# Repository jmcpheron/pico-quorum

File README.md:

<p align="center">
  <picture>
    <source media="(prefers-color-scheme: dark)" srcset="docs/brand/lockup-dark.svg">
    <source media="(prefers-color-scheme: light)" srcset="docs/brand/lockup-light.svg">
    
  </picture>
</p>

<p align="center">
  <strong>Several people, several keys, one Safe.</strong><br>
  Hardware approvals for <a href="https://safe.global">Safe</a> multisig wallets.
</p>

<p align="center">

  <br>

  <br>

</p>

Picoquorum is a small console that is **one owner of a Safe**. Each signer holds a plug-in key with a
secure element inside. The console shows what a transaction does on its own screen, works out the
Safe transaction hash itself, and asks the key to sign only after you have seen every page and held
the green **Sign** button. **Reject** is red and easy.

The same console also runs [in your browser](https://picoquorum.app/console/), with
your own passkey as its key. That version is one short folder you can read, check against this
README, and sign from on your own computer.

### A pico quorum

A *pico quorum* is a small group that agrees before anything moves: a family's savings, a club's
treasury, a two-person company, a project's release keys. Two of three. Three of five. Too small for
a custody desk, too important for one laptop. Picoquorum gives each person in that group the same
small box and their own key, and makes every approval a deliberate thing you do with your hands.

> **Experimental.** Early design. Use a testnet first, and only small amounts on mainnet. The Safe's
> threshold is the real control: always keep owners on the Safe that are not this console.

## Four ideas

### 1. A key that can't leak

The key is a secure element on a small board you plug in. Its P-256 private key is generated inside
the chip, never leaves it, and never exists as a seed phrase. There is nothing to write down,
photograph or phish. The chip has no command that reads a private key out, it is locked after
provisioning, and the console asks it to sign only a hash the console worked out itself.

Each key owns the Safe through Safe's audited passkey signer
([`firmware/webauthn.py`](firmware/webauthn.py)), with the same owner address on every chain. The
contracts it relies on were checked onchain on Base and Ethereum.

**The USB-C key, in production now.** [key-c P2](hardware/key-pcb/key-c-usbc/README.md) is the key
as a part you can hold: an ATECC608C behind a USB-C receptacle on a 16 × 36 mm board, with an ESD
array between the connector and the chip.
- The receptacle is plain wires, not USB: D+ carries SDA, D− carries SCL, and VBUS is key power
  that the console switches on only when the key is fully in.
- 5.1 kΩ on each CC pin tells the console a key is present.
- Five boards are being assembled at JLCPCB; the first bench bring-up is next.

| parts side | back |
|---|---|
|  |  |

Until it arrives, the dev console's key is an Infineon OPTIGA Trust M or an ATECC608 breakout. The
other key designs (card edge, pogo pads) are in [`hardware/key-pcb/`](hardware/key-pcb/README.md).
How a chip is locked: [docs/LOCKING.md](docs/LOCKING.md) and [docs/TRUSTM.md](docs/TRUSTM.md).
What a sealed key can't protect you from: [docs/SECURITY.md](docs/SECURITY.md).

### 2. A simple console that checks on its own

The console is a Raspberry Pi Pico 2 W with a 240 × 240 screen and a few buttons, running a small
amount of MicroPython you can read. It doesn't take anyone's word for a transaction: not your
laptop's, not your browser's, not Safe{Wallet}'s, and not the transaction service's.

- **Its own hash.** It rebuilds the Safe's EIP-712 transaction hash from the fields it shows, for
  the chain and Safe it was set up for, and its key signs that hash and nothing else. A service
  that lies about the hash, the Safe or the chain gets a refusal, not a signature.
- **Its own words.** It decodes each call into plain language. Anything that changes who controls
  the Safe, or can't be undone, is a red page, red all over.
- **Its own screen.** You page through every screen before Sign is allowed, then hold it for two
  seconds. The verify code (the hash's last eight characters and its blockie) is there to check
  with whoever proposed it.
- **Its own path.** It talks to the transaction service over its own Wi-Fi and TLS, checking
  certificates against the roots it carries. Nothing on your computer is in the loop.

| | | | |
|---|---|---|---|
|  |  |  |  |
| **Plain language.** What it does, who it pays, who has signed. | **Red pages.** Owners, thresholds, anything that can't be undone. | **A verify code.** To check with the proposer. | **Hold to sign.** Two seconds on a guarded button. |

That independence is the point. A second check is only worth something if it fails differently from
the first: different hardware, different code, a different network path, a different person looking
at it. More screens: [docs/quorum-ui](docs/quorum-ui/README.md).

**The console on its own board.** [console-rp](hardware/console-rp/README.md) is
the console as one board: an RP2350A with no radio, a 1.14″ 240 × 135 screen, D0 D1 D2 under it,
and an ATECC608C on the board. Its USB-C reaches only a CH343P serial chip, never the RP2350's own
USB or its REPL.
- Five came assembled from JLCPCB on 2026-11-04. Four run the console's own image and one is
  broken ([the boards](hardware/console-rp/README.md#the-boards-and-the-firmware)).
- The owner makes the key on the board, and the console pins itself to that chip
  ([setting one up](hardware/console-rp/SETUP.md)).
- With no Wi-Fi, a relay on the computer fetches the Safe's queue and posts the console's
  signatures: `tools/relay/relay.py`, or the app's Device page. The console still rebuilds every
  hash itself ([the relay](docs/USB-LINK.md#the-relay-console-rp)).

### 3. One owner in a multisig

Picoquorum is never the whole wallet. It is one owner among several, and it is built to sit next to
the others: a hardware wallet, a passkey, Safe{Wallet} in a browser, another Picoquorum in another
house. The project's own Safe is planned around one rule ([docs/GOVERNANCE.md](docs/GOVERNANCE.md)),
and we suggest it for yours: **no technology, and no person, holds a threshold's worth of keys.**

- **Standard Safe.** Any Safe from 1.3.0 on, on Base and Ethereum. Propose anywhere; the console
  reads the same queue Safe{Wallet} does.
- **The app** ([launch it](https://picoquorum.app/app/)) opens any Safe, proposes,
  checks every confirmation in your browser, and executes with your wallet. It holds no key.
- **Several Safes, several chains.** One console watches up to 4 Safes on Base Sepolia, Base and
  Ethereum, with one queue across them ([networks](docs/guide/NETWORKS.md)).
- **A pico quorum per Safe.** A family Safe at 2 of 3, a team Safe at 3 of 5, each owner with a
  console and a key of their own.

### 4. A short stack you can check yourself

[The console page](https://picoquorum.app/console/) runs the console's firmware,
file for file, on MicroPython for WebAssembly, with your passkey (Touch ID, Windows Hello, a phone,
a security key) as its key. It is one folder, it loads nothing from the rest of the site, and it can
reach only Safe's transaction service: its Content-Security-Policy says so, and the browser enforces
it.

| in the folder | |
|---|---|
| `firmware/` | the console image a Pico runs, as plain files: about 11,000 lines of MicroPython |
| `shims/` | Python in place of the Pico's hardware: about 630 lines |
| `console.js`, `worker.js`, `web/`, `core/` | the page: about 1,100 lines of JavaScript |
| `vendor/micropython/` | MicroPython 1.26 for WebAssembly, pinned by its hash: the one part built elsewhere |

That is short enough to read, and you can check it without trusting the site that sent it:
- **Save a copy.** `SHA256SUMS` lists every file: fetch them, then `sha256sum -c SHA256SUMS`. There
  is no build step; these are the files that run.
- **Hold it up to this README.** `firmware/`, hashed with `sha256sum` in a one-line loop, gives the
  console's release fingerprint in [the build table](#the-build-youre-looking-at): the same one a
  Pico running that release shows on its Device screen.
- **Rebuild it.** `cd emu && npm ci && node build.mjs` writes the same bytes. CI checks that on every
  push, and a check from outside compares what Pages serves with the source every six hours.
- **Sign from your copy.** Run `python3 -m http.server` in the folder and open `localhost:8000`. A
  passkey belongs to the site that made it, so one made on your copy can be asked to sign by your
  copy and never by a later version of the site. Its owner address works on a Safe like any other.

The commands: [docs/guide/BROWSER.md](docs/guide/BROWSER.md). The screen is still drawn by your
computer, and the passkey's prompt never shows the transaction, so the hardware console is the
stronger owner: keep passkey owners below the threshold.

## Try it

- **[The site](https://picoquorum.app/)**, with the app.
- **[The console in your browser](https://picoquorum.app/console/)**: the same
  firmware in MicroPython on WebAssembly, with your own passkey as its key. Save it, check it and
  run your own copy ([how](docs/guide/BROWSER.md); the design: [EMU-WEB.md](docs/EMU-WEB.md)).
- **[Learn](https://picoquorum.app/learn/)**: short explainer videos on why a multisig and what the
  console adds to one. The videos are on their way; [their scripts](docs/videos/README.md) are here
  to read.
- **[The owner's guide](docs/guide/README.md)**: from a board to a console that signs for your
  Safes.
- **Build a dev console**: a Pico 2 W, a Waveshare Pico-LCD-1.3 and an ATECC608 breakout, about
  $35 with no soldering ([build guide](hardware/DEV-CONSOLE.md), [parts](hardware/bom/README.md)).
- **On a laptop**, no hardware: `tools/quorum e2e` runs a whole approval with the emulator against a
  Safe 1.4.1 on an Anvil fork of Base ([details](tools/mock-tx-service/README.md)).
- **The hash, checked**: `python3 test-vectors/run.py` runs every vector in
  [`test-vectors/`](test-vectors/), including real mainnet Safe transactions, on CPython; CI runs
  them on MicroPython 1.26 too.

## The build you're looking at

Every firmware image has a **release fingerprint**: one SHA-256 over its source files
([docs/releases](docs/releases/README.md)). A console shows its blockie and first 8 hex digits on the
Device screen; the console page shows the same picture for the same files, and its `firmware/`
folder hashes to it with `sha256sum` ([how](docs/guide/BROWSER.md#2-hold-it-up-to-the-readme)); the
app's Releases page lists each release's. The badges above and this table name the source in this commit, so you can hold a
console up to the README:

<!-- build:begin (node tools/releases/badge.mjs writes this table) -->

| | image | release fingerprint |
|---|---|---|
|  | **console** | `c79cac3145ff41a832656c4eeebad22e4f8dc3719f27e9f5acd9be9e41572275` |
|  | **ceremony** | `381d4e8916ea331b7b8a8ef650b28c5a45d35c116fe40969c8f5c66cea223ec2` |
|  | **brand** | `f7b49688d24a2ce8dbc4f5af474a708f4b043af84049aa9b56221c76f1b9ceb3` |
|  | **dual** | `99292ecee02cdcabfd1714b7c16ab250634345925e9c6cd2764c10589be48d55` |
|  | **console-rp** | `f24d22db5f3916c11f6bbcc5a934885ea6593c7a132d318e042c1f4617094505` |
|  | **prepare-rp** | `4e98165819acdbb148753a1e73cb04bb83bec7861b4263e9246b60531162999f` |

<!-- build:end -->

How a release is trusted ([docs/RELEASES.md](docs/RELEASES.md)):
- **Signed tags.** A release is an SSH-signed tag, `fw-<version>`, checked against
  [`.github/allowed_signers`](.github/allowed_signers) before anything is built.
- **Reproducible pages.** CI rebuilds the app and the console page from source and fails if they
  differ from what is committed. The site check then compares what GitHub Pages serves, byte for byte,
  with the commit it deployed.
- **Approved by a Safe.** The project Safe will approve each release on chain, signed on Picoquorum
  consoles, and the app then shows **Approved by the project Safe**. The code is ready; the Safe
  comes at launch ([docs/GOVERNANCE.md](docs/GOVERNANCE.md)).

## Where it stands

Picoquorum is built in public. **[docs/STATUS.md](docs/STATUS.md)** is the one page for what exists
today: the name (picoquorum.eth) and the domains, every Safe and key with its address, the contracts
the console relies on, and what's next.

**Now:** [console-rp](hardware/console-rp/README.md), the one-board console with no radio. Its
firmware runs on four boards and is in review (pull request #113).

The [test ladder](docs/LADDER.md) tracks each chain:
- ✅ a simulated Safe and a local fork, on the real Pico
- ✅ Base Sepolia, end to end over HTTPS on the real Pico
- Base with a few dollars: the Safe is checked and a chip's confirmation has executed there; the
  console's own approval is next
- then Ethereum mainnet, whose contracts have been checked onchain

The design and the open questions are in the [kickoff](docs/KICKOFF.md), and the project Safe's plan
in [GOVERNANCE.md](docs/GOVERNANCE.md). Dated notes and photos, mistakes included, are in
[`buildlog/`](buildlog/).

## Layout

| path | what |
|---|---|
| `firmware/` | the console in MicroPython: `quorum.py` and `quorum_ui.py` (the console), `safe_tx.py` (the Safe hash), `decode.py`, `txservice.py`, `webauthn.py`, the chip drivers `trustm.py` and `atecc.py` |
| `hardware/` | `console-rp/` ([the one-board console](hardware/console-rp/README.md)), `key-pcb/` (the keys, [key-c](hardware/key-pcb/key-c-usbc/README.md) among them), `wiring/` ([Build 1](hardware/wiring/BUILD1.md), [perfboard](hardware/wiring/SOLDERING.md), [breadboard](hardware/wiring/BREADBOARD.md), [on an ESP32](hardware/wiring/ESP32.md)), `bom/` |
| `docs/` | everything to read ([index](docs/README.md)), and the site GitHub Pages serves: the front page, `app/`, `console/`, `brand/` |
| `web/` | the app's source; `npm run build` writes `docs/app/` |
| `emu/` | the console in a browser: MicroPython in WebAssembly and a virtual secure element. `build.mjs` writes the console page (`docs/console/`); `tools/emu` adds an editor and the case in 3D, for development |
| `test-vectors/` | Safe transactions with known-correct hashes, and the suites CI runs |
| `tools/` | `quorum` (Safes on a fork and on chain), `fw` (build and push images), `emu`, `usb`, `release`, `releases/`, `brand/`, `keypcb`, `wiring`, `wiring-esp32` |
| `contracts/` | Picoquorum's own contracts, when there are any; today each key owns a Safe through Safe's passkey signer |
| `buildlog/` | dated notes and photos |

The name, the mark and the colours: [docs/BRAND.md](docs/BRAND.md). `tools/brand/lockup.py` draws the
logo at the top of this page.

## Credit

Picoquorum exists because of [picowallet](https://github.com/austintgriffith/picowallet) by
**Austin Griffith**. picowallet proved that a Raspberry Pi Pico can drive a secure element from
MicroPython, rebuild an EIP-712 digest on the device, show it on its own screen, and sign with a
key that never leaves the chip, all on mainnet. Picoquorum began as a fork of it and is still
built on it:
- the ATECC608 and Trust M drivers, the display driver, keccak and P-256, blockies and the WiFi join;
- the emulator that runs the console in your browser.

Each of those files says so on its first line, under Austin's MIT license. Fixes to the drivers go
back upstream ([docs/UPSTREAM-TRACKING.md](docs/UPSTREAM-TRACKING.md)). Everything else this project
uses is credited in [NOTICE](NOTICE).

Picoquorum runs on Raspberry Pi Pico 2 W. It is not affiliated with Raspberry Pi or Safe.

## License

| | license |
|---|---|
| Code and firmware: `firmware/`, `emu/`, `web/`, `tools/`, `test-vectors/`, the built site | [MIT](LICENSE) |
| Hardware: `hardware/` (the key boards, wiring, parts lists) | [CERN-OHL-W-2.0](LICENSE-HARDWARE) |
| Docs, the build log, photos and screenshots | [CC BY-SA 4.0](LICENSE-DOCS) |
| The name Picoquorum and its mark | not licensed: [TRADEMARK.md](TRADEMARK.md) |

Hardware made from these sources must show where the source is ([hardware/README.md](hardware/README.md#license)).
Third-party parts and their licenses are in [NOTICE](NOTICE).

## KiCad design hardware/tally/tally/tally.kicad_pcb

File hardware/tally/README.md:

# Tally: a second take on Mono's idea, with no inductor

*Design, 2026-11-13. Written by a script, [gen_tally.py](gen_tally.py), with KiCad 7.0.11: KiCad
reads the schematic back (netlist) and runs its DRC on the routed board, and both come out clean.
Ten agents then reviewed it; what they found and what was changed is in [REVIEW.md](REVIEW.md).
The repo's own checks (`tools/keypcb check` and `jlc`) want KiCad 10 and were **not run**: see
[What is checked, and how](#what-is-checked-and-how). Not ordered, nothing built, no panel folded
against it, and no firmware profile for it yet. Tally is a working name.*

*The board file's front copper, drawn by a throwaway plotting script that is not in the repository
(KiCad 7 has no 3D render; `tools/keypcb render tally` will make proper ones on KiCad 10). Blue is
signal, red 3.3 V, orange 1.1 V, purple 5 V, grey ground. Pale lines are on the back.
[The back](renders/tally-back.png), seen through the board, is in the same folder.*

Tally is an independent design of the same console as [Mono](../mono/README.md): a 40 × 89.5 mm
bar with no radio, the key soldered on, a small screen for clear signing and three buttons. It
starts from Mono's outline and pins and makes its own choices where Mono's parts are hard to buy or
its first relative, console-rp, misbehaved.

```
   computer (the relay) ── USB-C ── CH343P ── UART1 ── RP2350A ── I2C0 ── ATECC608C (the key that signs)
   no key, no say in                                  │
   what gets signed                                   └─ SPI1 ── 1.14" panel;  D0 D1 D2
   firmware goes in over SWD only: J3 on the front, pads on the back, 100 Ω in each line
```

The computer can't reach the RP2350's REPL, reset it or hold BOOTSEL: the CH343P's modem pins go
nowhere, and the RP2350's own USB pins go nowhere either. The generator checks both
([The link](#the-link)).

## What is different from Mono, and why

| | Mono | Tally | why |
|---|---|---|---|
| the core's 1.1 V | the RP2350's switching regulator: Abracon inductor, 33 Ω, three capacitors | a fixed 1.1 V LDO, **TLV74311PDBVR**, from 3.3 V; one capacitor at the chip's regulator pins | the inductor is the hardest part to buy (JLCPCB 756, LCSC 0, one maker, polarity matters). console-rp's board 1 read 1.4 V on DVDD where 1.1 V is expected, and nobody knows why. An LDO has nothing to lay out wrong. It costs about 0.14 W more from USB at 45 mA of core current |
| the crystal | Abracon ABM8-272-T3, the one Raspberry Pi names | YXC **X322512MSB4SI** (C9002) on Raspberry Pi's 15 pF and 1 kΩ | JLCPCB has 1 of the Abracon, LCSC 0. The YXC is a Basic part with 494,234 in stock. Not Raspberry Pi's tested part: see [Open](#open) |
| the chip's own USB, BOOT | on pads, through 27 Ω and 1 kΩ | **not connected** | console-rp's own USB never enumerated; SWD is how its board 1 was loaded. Three parts and three pads fewer, and one less way in. It has a cost: see [Open](#open) |
| the debug way in | pads for a pogo jig | the same pads at Mono's places, and **J3**, Raspberry Pi's 3-pin JST-SH debug socket | a Debug Probe's cable plugs in. No jig is needed for the first boards |
| the second key's site | KEY 2: a footprint, a switched supply, a header | none | not needed for a first product |
| the USB-C | left of centre | centred | the bridge and the ESD diodes sit in line above it |
| on VBUS | 5.7 µF | 11 µF, as console-rp | WCH asks for 10 µF beside a CH343P fed from VBUS, whose limit is 6.0 V. See [Open](#open) |
| the link's idle level | none until the firmware drives it | 4.7 kΩ to 3.3 V on the chip's TX | the bridge sees a clean idle while the chip is in reset or blank |
| the backlight's driver | an NPN and a base resistor | an N-FET, AO3400A | one part fewer |
| parts | 87 on the drawing, 67 fitted | 70 on the drawing, **53 fitted**, of 25 kinds | |

Kept: the outline, the four M2 holes, the glass and the three buttons where Mono has them; the
RP2350A with Raspberry Pi's copper round it (`rpi_minimal.json`, MIT,
[lib/RPI-MINIMAL-LICENSE.txt](lib/RPI-MINIMAL-LICENSE.txt)); the CH343P link; the ATECC608C in
SOIC-8; the ZIF and the panel; the LDL1117S33R; the backlight fed from 5 V; and **every GPIO**
([PINS.md](PINS.md)), so one board profile can serve console-rp, Mono and Tally.

**Mono's case does not fit as it is.** The board's outline, holes, glass and buttons are Mono's.
The USB-C's opening moves to the middle, the LED is 66.5 mm from the top where Mono's is 71, and
J3 opens toward the left wall. `cad/consoles/mono.py` was not run on Tally and stops on it today
(it has no size for J3's package).

**An ESP32 instead?** No. Every ESP32 that JLCPCB can solder has a radio on the chip except the
ESP32-P4, which needs Standard assembly, costs $5.41, and had 111 in stock. The RP2350A has no radio
on the chip, costs $1.23, and the firmware already runs on it.

## The core's supply

The RP2350 datasheet (section 6.3.7, figure 24) allows it: "If the digital core supply (DVDD) is
powered from an external 1.1 V supply, the on-chip regulator can be disabled and the application
circuit simplified. Power must still be provided on the regulator's analogue supply (VREG_AVDD)
and input supply (VREG_VIN) ... But the inductor can be omitted and only a single input capacitor
is required. Connect VREG_FB directly to ground."

So on Tally:
- VREG_VIN (pin 49) and VREG_AVDD (pin 46) are on 3.3 V with C20, 4.7 µF.
- VREG_FB (pin 50) and VREG_PGND (pin 47) are on ground. VREG_LX (pin 48) is open.
- U4 feeds the three DVDD pins: 4.7 µF at its output, 100 nF at pins 6 and 39, 4.7 µF at pin 23.
- TP10 on the back is DVDD, to put a meter on.

**What the firmware must know**, which it need not on Mono:
1. **Never let the regulator go to its low-power mode.** The datasheet: "Don't put the regulator
   into low-power mode if DVDD is being powered from an external supply." That mode is the reset
   default for the P1.x sleep states (`VREG_LP_ENTRY.MODE` resets to 1). `firmware/` uses no sleep
   today. Before any is used on this board, write `VREG_LP_ENTRY` with HIZ 1 and MODE 0, and find
   out what MicroPython's `lightsleep` does on an RP2350.
2. **`VREG.HIZ` is optional, and not for a shared image.** Left alone, the chip's regulator stays
   on with nothing to drive: "a safe mode of operation, though the regulator will consume
   approximately 400 µA until it's shut down". An image only for Tally can write 1 to `VREG.HIZ`
   on every boot (it does not survive a reset). On Mono or console-rp the same write takes the
   core's supply away: "If the on-chip regulator is supplying DVDD, entering high-impedance mode
   causes a reset event". So an image shared by the three must not write it.

The TLV74311P is ±1.4 % over temperature by its datasheet, so 1.085 to 1.115 V, inside the chip's
1.05 to 1.16 V. It gives 300 mA. Its heat is (3.3 − 1.1) V × the core's current: about 0.1 W at
45 mA. How it holds up under the core's load steps was not measured or simulated.

## The link

The same as Mono's. The USB-C's D+ and D− go through the USBLC6-2SC6 to the CH343P and stop. The
CH343P's TXD and RXD go to GPIO21 and GPIO20 (UART1) and to two pads on the back, to watch the
link. R13 pulls the chip's TX to 3.3 V, so the bridge sees an idle line before the firmware runs.
`gen_tally.py` stops if:
- any pin of the CH343P is on another net than its name allows: TXD on LINK_RX, RXD on LINK_TX,
  VIO on 3.3 V, and DTR, RTS, ACT, DCD, DSR, CTS and RI on nothing at all;
- the RP2350's USB_DP or USB_DM is connected at all;
- the USB-C and the RP2350 share any net but ground;
- any of 23 nets reaches a part that is not on its list: D+, D−, both CC lines, the bridge's V3,
  the link's two lines, SWCLK and SWDIO on each side of their resistors, RUN, the key's bus, the
  three buttons and the flash's six lines.

## The front, top to bottom

- **The panel**, a 1.14-inch 240 × 135 ST7789 (ER-TFT1.14-2) on tape, where Mono has it. Its ribbon
  folds under into J2. Only J2 and two capacitors are under the glass. Four silkscreen corners
  show where the glass goes.
- **D0, D1, D2**, 10 mm apart, 24 mm from the top, as Mono.
- **The backlight's switch** on the left: Q2 (GPIO13, 4.7 kΩ to ground) pulls Q1's gate; Q1 feeds
  the LED from 5 V through 150 Ω, about 13 mA. High is on.
- **The key**, U6, under D1, with its pull-ups and capacitor.
- **The RP2350A**, turned a quarter turn, and **the flash** beside it.
- **U4**, the 1.1 V regulator, under the chip.
- **The red LED** (GPIO25), 66.5 mm from the top.
- **J3**, the debug socket, on the left edge, with 100 Ω in SWCLK and SWDIO.
- **The bridge, the ESD diodes and the USB-C** in line at the bottom; the 3.3 V regulator beside them.

Nothing is fitted on the back. It has the pads and the text.

## The pads on the back

| pad | net | |
|---|---|---|
| TP1, TP2, TP3 | SWCLK, GND, SWDIO | at Mono's places, 2.54 mm apart; on J3's side of the 100 Ω |
| TP4 | RUN | low resets the chip |
| TP5, TP9 | 3V3, GND | to measure |
| TP10 | 1V1 | the core's supply |
| TP11 | VBUS | |
| TP12, TP13 | TX, RX | the link, to watch with a logic probe |

Mono's BOOT, D+ and D− pads have no twin here. No pad has a via at its centre, so a pogo pin lands
on copper.

## Parts at JLCPCB

Read from JLCPCB's and LCSC's listings on 2026-11-13. Stock and prices move daily.

| | part | LCSC | tier | JLCPCB stock | each |
|---|---|---|---|---|---|
| U1 | RP2350A | C42411118 | Extended | 5,813 | $1.29 |
| U7 | W25Q128JVSIQ, 16 MB | C97521 | Basic | 70,193 | $2.26 |
| U6 | ATECC608C-SSHDA-T | C28975195 | Extended | 3,664 | $1.75 |
| U5 | CH343P | C2846043 | Extended | 18,478 | $1.00 |
| U3 | LDL1117S33R | C435835 | Extended | 53,806 | $0.49 |
| U4 | TLV74311PDBVR | C485147 | Extended | 10,900 | $0.07 |
| U2 | USBLC6-2SC6 (ST) | C7519 | Extended | 43,645 | $0.16 |
| J1 | TYPE-C-31-M-12 | C165948 | Extended | 539,075 | $0.19 |
| J2 | 0.5K-HX-8PWB | C2919492 | Extended | 13,441 | $0.10 |
| J3 | SM03B-SRSS-TB | C160403 | Extended | 26,795 | $0.19 |
| Y1 | X322512MSB4SI, 12 MHz | C9002 | Basic | 494,234 | $0.10 |
| Q1, Q2 | AO3401A, AO3400A | C15127, C20917 | Basic | over 1,000,000 each | $0.08 |
| SW1 to SW3 | TS-1187A-B-A-B | C318884 | Basic | 826,275 | $0.02 |
| the rest | 24 capacitors, 12 resistors, 1 LED, all 0402 but four | | Basic | | $0.17 together |

- **About $8.00 of parts a board**, at JLCPCB's price for one.
- **Nine Extended kinds.** On Economic assembly that is 9 × $3.07, with $8.18 setup, $1.53 stencil
  and $0.45: about $38 an order before boards, parts and joints.
- **Two fees could go.** J3 can be left off the BOM (the pads on the back do the same job with a
  jig). JLCPCB lists an SRV05-4 (C7420376) as a Preferred part with no fee, in the USBLC6's package;
  its maker is not ST and its pinout was not checked here, so Tally keeps the ST part.
- **With the flash inside the chip.** `BUILD = "RP2354A"` in the generator fits an RP2354A
  (C41378174, 1,418 in stock, $1.24 at ten) and leaves U7 and its capacitor off: about $2.30 less a board.
  It has 2 MB, so it needs a MicroPython build told so; the stock Pico 2 image assumes 4 MB. The
  default stays the RP2350A with the 16 MB flash, which is what console-rp's board 1 ran.
- The panel is not JLCPCB's: 100 ER-TFT1.14-2 were bought at $3.71.
- **Placement angles.** JLCPCB lays its own footprint for each part on the CPL's point. Eight of
  them have pin 1 in another corner than KiCad's: U2, U4, U5, U6 and U7 need a quarter turn, and U3,
  Q1 and Q2 a half. `cpl.csv` carries those turns. The schematic has them as the field
  `JLCPCB Rotation Offset`, which `tools/keypcb fab` reads too. J1's point is where JLCPCB's
  footprint has its origin, 1.4 mm from KiCad's. All of it comes from JLCPCB's own footprints,
  laid pad for pad on KiCad's, four times over; the published rotation tables agree but for U4
  ([REVIEW.md](REVIEW.md#the-placement-file)). None of it is proven on a board. In JLCPCB's
  placement preview, hold each IC's dot against the silkscreen's mark before paying: **U5 and U1
  first**, where a wrong quarter turn fits every pad; then U6, U7, U2 and D1; then U4.

## Routing

Two layers, 0.15 mm least track and gap, 0.6 mm vias with 0.3 mm holes. Every track is drawn by
the script, by coordinates: nothing was autorouted.
- **Round the chip** the copper is Raspberry Pi's, turned with it: the 3.3 V and 1.1 V rings under
  the chip, each supply pin's track to its capacitor, the crystal's corner. Their switching
  regulator's corner is left out.
- **The back is ground**, with these tracks on it: the 1.1 V tracks under the chip (Raspberry Pi's);
  D0, 18 mm from the chip to the left button; the key's 3.3 V, 8 mm; the screen's DC, 5 mm under the
  glass; 5 V across the bridge; D− for 4 mm under the USB-C; and stubs to five pads. Three of them
  exist because GPIO2, 3 and 6 leave the chip in the opposite order to D0, D1, D2, and Tally keeps
  Mono's pins rather than untangle them.
- **90 ground vias** join the two pours on a 4 mm grid, and one more sits beside each capacitor the
  grid left far from one.
- **5 V runs up the left edge** to the backlight's switch, about 55 mm of 0.25 mm track at 13 mA. It
  passes under R11 between its pads.
- The screen's six lines run 25 mm side by side. SCK has 0.5 mm to its neighbours.

## What is checked, and how

Run here, with KiCad 7.0.11 on Linux, on 2026-11-13:
- `python3 gen_tally.py`: writes everything, then checks it. `python3 gen_tally.py check` checks
  the files as they are. Two runs give the same bytes.
- **The table against itself:** each GPIO can do the job it is given (SPI1, I2C0, UART1); the
  screen's and key's pins are `firmware/board.py`'s Pico defaults; the link's rules above.
- **KiCad's netlist of the schematic against the table:** every net has exactly the pins the table
  lists, every part its value, footprint and LCSC number.
- **The board against the netlist:** every pad on its net, every schematic pin on a pad, every part
  at its place and side.
- **KiCad's DRC on the routed board**, with the project's rules: 0 violations, 0 unconnected.
- **fab/, the project file and PINS.md:** each written again into a temporary folder and compared
  (the Gerbers with their date lines left out).
- **Six broken copies** (TXD and RXD swapped, two screen pins swapped, PINS.md edited, every DRC
  severity set to ignore, the zip replaced, a pad cut from a footprint): the check stops on each.
- **A review** by ten agents: [REVIEW.md](REVIEW.md). It read the Gerbers back with an unmodified
  copy of `tools/jlc/gerb_check.py` and ran `tools/jlc/netlist_check.py` on the BOM and CPL.

Not run, and why:
- **`tools/keypcb check tally` and `tools/keypcb jlc tally`** (KiCad 10's ERC, DRC with schematic
  parity, JLCPCB's limits, the 3D fit). They need KiCad 10. This session could not install it:
  adding KiCad's package source and running its Docker image were both refused by the session's
  permissions. `tools/keypcb` knows the board, so a bare `tools/keypcb check` now includes it.
  `gen_tally.py` has a `jlc_spec()` for it, written by Mono's keys and never executed.
- **KiCad's ERC.** KiCad 7's command line has none.
- **`gen_tally.py` under KiCad 10's Python**, which is how `tools/keypcb gen-tally` runs it. It was
  written and run on KiCad 7's. Five calls that changed names are handled; others may not be.
- **A 3D render or the case.**
- **Anything electrical.** No simulation, no board.

## Steps to a board

1. On a machine with KiCad 10: `tools/keypcb gen-tally check`, `tools/keypcb check tally`, then
   `tools/keypcb fab tally` and `tools/keypcb jlc tally`. Fix what they find. `tools/keypcb fab`
   rewrites `tally/fab/`; `gen_tally.py check` accepts its files.
2. Measure a real panel's ribbon in a real J2 (Mono's README, "The panel"). Tally's J2 is where
   Mono's is, 19.5 mm in from the glass's ribbon end. By the connector's drawing the ribbon may want
   it about 1.2 mm further in; console-rp's sits further out and works with a loop.
3. Decide the first two things under [Open](#open).
4. Order five on Economic assembly: 2 layers, 1.6 mm, lead-free HASL, or ENIG for the 0.4 mm QFN.
   Pay for "Confirm Production file" to see where JLCPCB puts its tooling holes and rails. In the
   placement preview, hold each IC's dot against the silkscreen's mark.
5. Bring-up, in this order:
   - 5 V and 3.3 V with nothing else; **1.1 V on TP10 before anything else**.
   - SWD on J3 with a Debug Probe; then console-rp's bench scripts.
   - The crystal: read `XOSC.STATUS` on every board, and again cold.
   - A scope on TP11 at plug-in with a short thick cable: VBUS must stay under 6.0 V.
   - VBUS ramped from 0 to 5 V over 0.1, 1 and 5 s, and cut for 0.3 to 2 ms: it must boot each time.
   - `lsusb -v`: the bridge's `bMaxPower` against a draw of about 80 mA, 150 mA at peaks.

## Open

- **The chip's own USB is not brought out.** `picotool`'s OTP commands work only over that USB, so
  turning on secure boot later would need a program loaded over SWD instead. And once SWD is closed
  in OTP, a board with no USB and no BOOT pad cannot be loaded again at all. If secure boot is on
  the road, put Mono's three pads back: two 27 Ω resistors, 1 kΩ, three pads, and three thin tracks
  past C19. Ask and it is a small change.
- **The crystal is not Raspberry Pi's.** They ask for the ABM8-272-T3 by name: 10 pF, 50 Ω at most.
  The YXC part is 20 pF and 80 Ω at most. On Raspberry Pi's 15 pF and 1 kΩ it will run 50 to 100 ppm
  fast, which nothing here minds (the UART tolerates percent; the chip's USB is not used). It also
  needs 1.6 times the gain to start, and the chip's gain is not published: an unknown margin, not a
  known fault. Test it as in the steps above before ordering more than five. The footprint takes the
  Abracon, or a 10 pF part (JLCPCB lists C5310728 and C50430, both Extended), with no other change.
- **The firmware.** No profile exists for this board or for Mono. It needs the pins, the 240 × 135
  screen at MADCTL 0x60, and what "The core's supply" says. Three things in today's code would bite:
  an unknown board name falls back to a profile that reads GPIO20 and GPIO21, here the link, as keys;
  `usblink.py` talks to the chip's own USB, which reaches nothing here, so the link must be opened as
  `UART(1, tx=20, rx=21)` (MicroPython's UART1 default pins are the key's bus); and maintenance uses
  a REPL on that USB, so until one is designed for UART1 every firmware change goes in over SWD. A
  new image is a new release fingerprint.
- **VBUS at plug-in, two ways.** 11 µF sits on VBUS, where USB allows 10 µF, because the bridge's
  supply pin has a 6.0 V limit and WCH asks for 10 µF beside it; console-rp has the same and works,
  and Mono has 5.7 µF. The charge taken at plug-in, with what fills through the two regulators, is
  about 125 µC by the capacitors' printed values, against USB-IF's 50 µC mark. Neither the overshoot
  nor the charge was measured. C1 can go back to 4.7 µF with no other change.
- **Nothing holds the chip in reset until 3.3 V is in range.** Its reset watches the core's supply
  only, and U4 makes 1.1 V from 1.4 V up. A gap in VBUS of about a millisecond can leave the core
  running while the flash is below its range: a hang that a replug cures. A supervisor on RUN would
  close it. None is fitted; test first.
- **No fuse and no TVS on VBUS** beyond the USBLC6's clamp, as Mono.
- **The 3.3 V regulator's tab** is its output and has no large pour. At 0.11 A it makes about 0.2 W.
- **Under USB suspend nothing drops**: the RP2350 can't see the bus. About 80 mA is drawn always.
- **The name.**

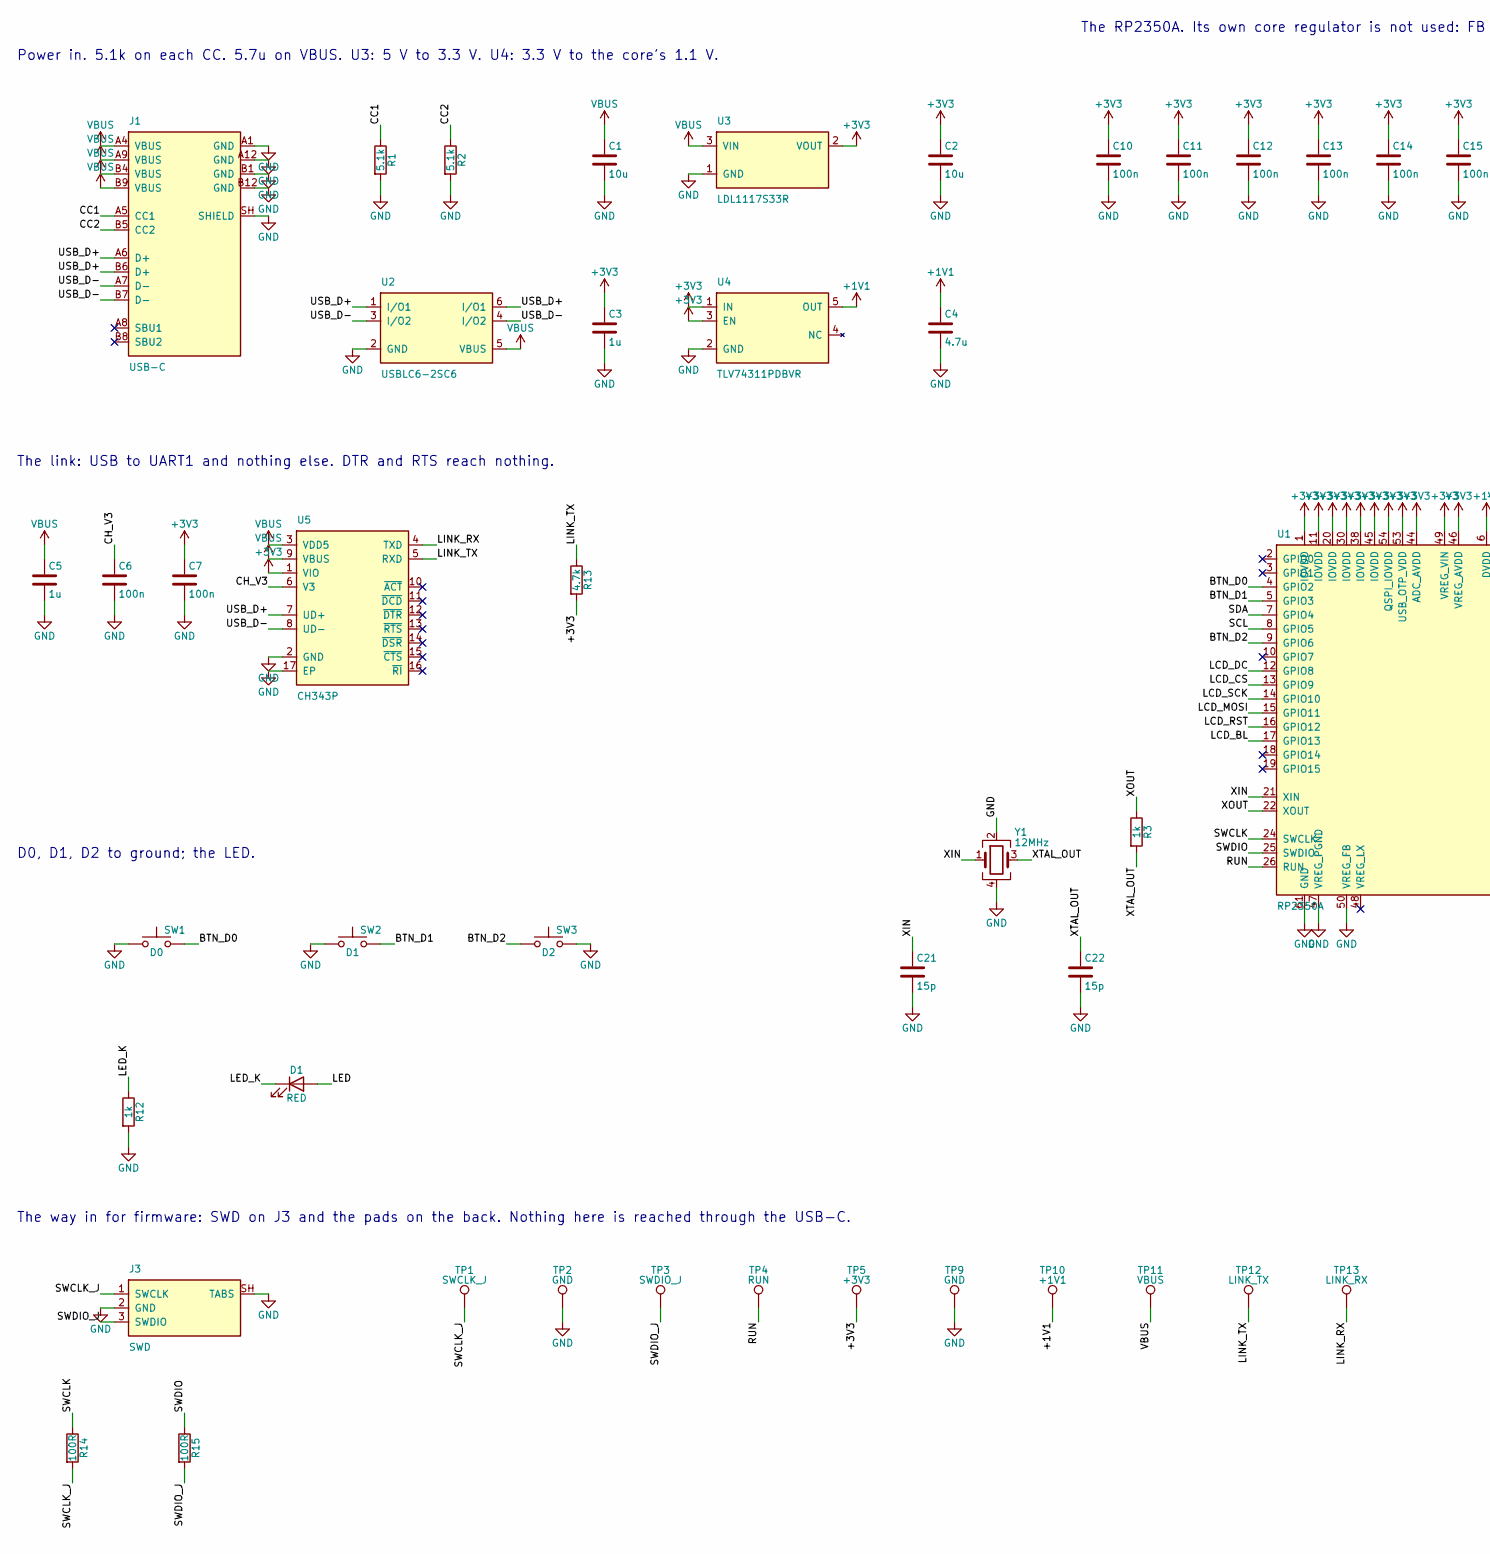
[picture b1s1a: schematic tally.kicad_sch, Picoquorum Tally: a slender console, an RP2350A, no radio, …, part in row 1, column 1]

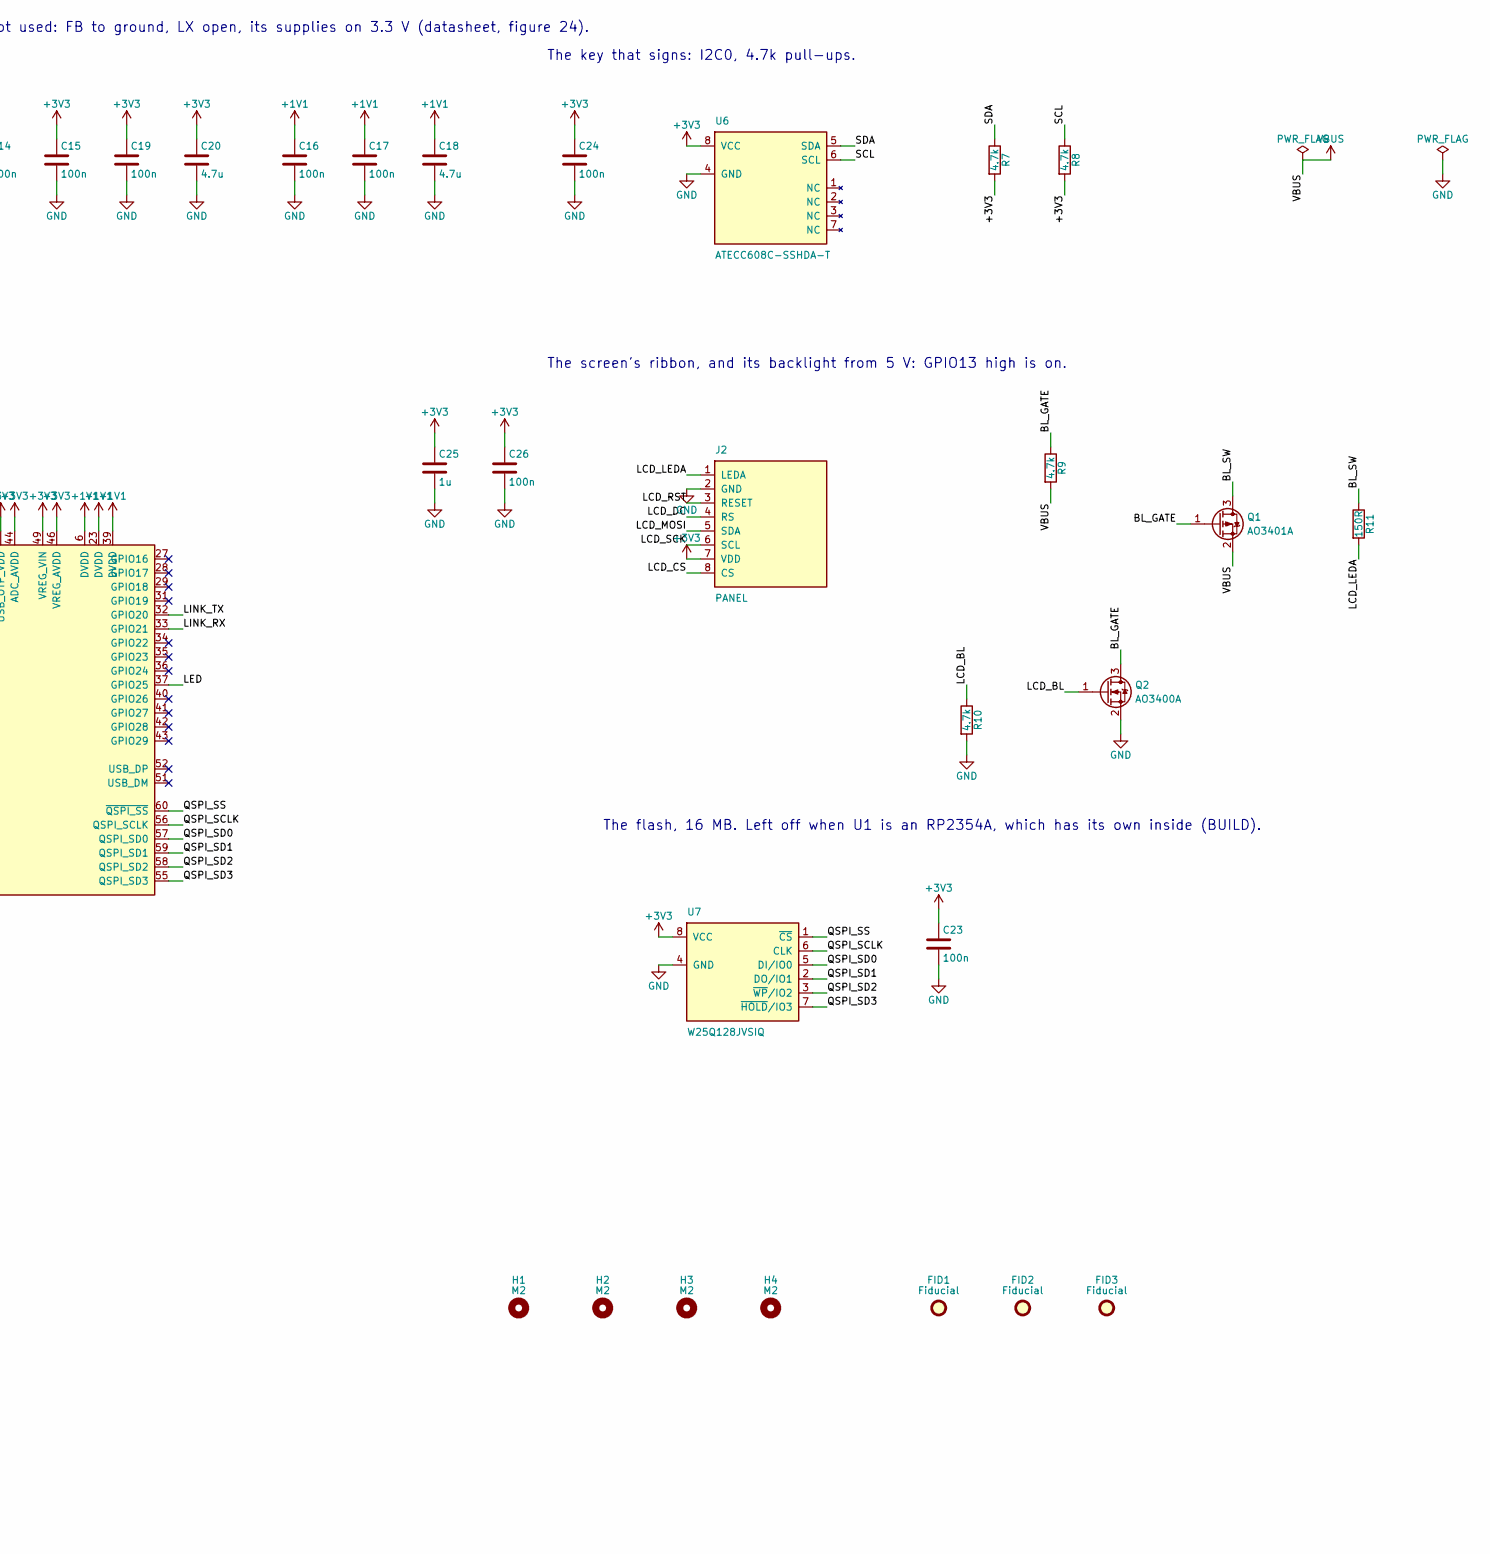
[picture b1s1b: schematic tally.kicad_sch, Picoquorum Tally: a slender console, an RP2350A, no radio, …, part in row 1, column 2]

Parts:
C1, C2: 10u; C_0805_2012Metric; MPN CL21A106KAYNNNE; LCSC C15850
C3, C5, C25: 1u; C_0402_1005Metric; MPN CL05A105KA5NQNC; LCSC C52923
C4: 4.7u; C_0402_1005Metric; MPN CL05A475MP5NRNC; LCSC C23733
C6, C7, C23, C24, C26: 100n; C_0402_1005Metric; MPN CL05B104KO5NNNC; LCSC C1525
C10, C11, C12, C13, C14, C15, C16, C17, C19: 100n; RPi_C_0402; MPN CL05B104KO5NNNC; LCSC C1525
C18: 4.7u; RPi_C_0402; MPN CL05A475MP5NRNC; LCSC C23733
C20: 4.7u; RPi_C_0402_wide; MPN CL05A475MP5NRNC; LCSC C23733
C21, C22: 15p; RPi_C_0402; MPN 0402CG150J500NT; LCSC C1548
D1: RED; LED_0603_1608Metric; MPN KT-0603R; LCSC C2286
FID1, FID2, FID3: Fiducial; Fiducial_1mm_Mask2mm
H1, H2, H3, H4: M2; MountingHole_2.2mm_M2
J1: USB-C; USB_C_Receptacle_HRO_TYPE-C-31-M-12; MPN TYPE-C-31-M-12; LCSC C165948
J2: PANEL; FPC_ZIF_8P_P0.5mm_HDGC_0.5K-HX-8PWB; MPN 0.5K-HX-8PWB; LCSC C2919492
J3: SWD; JST_SH_SM03B-SRSS-TB_1x03-1MP_P1.00mm_Horizontal; MPN SM03B-SRSS-TB(LF)(SN); LCSC C160403
Q1: AO3401A; SOT-23; MPN AO3401A; LCSC C15127
Q2: AO3400A; SOT-23; MPN AO3400A; LCSC C20917
R1, R2: 5.1k; R_0402_1005Metric; MPN 0402WGF5101TCE; LCSC C25905
R3: 1k; RPi_R_0402; MPN 0402WGF1001TCE; LCSC C11702
R7, R8, R9, R10, R13: 4.7k; R_0402_1005Metric; MPN 0402WGF4701TCE; LCSC C25900
R11: 150R; R_0603_1608Metric; MPN 0603WAF1500T5E; LCSC C22808
R12: 1k; R_0402_1005Metric; MPN 0402WGF1001TCE; LCSC C11702
R14, R15: 100R; R_0402_1005Metric; MPN 0402WGF1000TCE; LCSC C25076
SW1: D0; SW_Push_1P1T_XKB_TS-1187A; MPN TS-1187A-B-A-B; LCSC C318884
SW2: D1; SW_Push_1P1T_XKB_TS-1187A; MPN TS-1187A-B-A-B; LCSC C318884
SW3: D2; SW_Push_1P1T_XKB_TS-1187A; MPN TS-1187A-B-A-B; LCSC C318884
TP1: SWCLK_J; TestPoint_Pad_D1.5mm
TP2, TP9: GND; TestPoint_Pad_D1.5mm
TP3: SWDIO_J; TestPoint_Pad_D1.5mm
TP4: RUN; TestPoint_Pad_D1.5mm
TP5: +3V3; TestPoint_Pad_D1.5mm
TP10: +1V1; TestPoint_Pad_D1.5mm
TP11: VBUS; TestPoint_Pad_D1.5mm
TP12: LINK_TX; TestPoint_Pad_D1.5mm
TP13: LINK_RX; TestPoint_Pad_D1.5mm
U1: RP2350A; RPi_RP2350A_QFN-60_7x7mm_P0.4mm_ThermalVias; MPN RP2350A; LCSC C42411118
U2: USBLC6-2SC6; SOT-23-6; MPN USBLC6-2SC6; LCSC C7519
U3: LDL1117S33R; SOT-223-3_TabPin2; MPN LDL1117S33R; LCSC C435835
U4: TLV74311PDBVR; SOT-23-5; MPN TLV74311PDBVR; LCSC C485147
U5: CH343P; WCH_QFN-16-1EP_3x3mm_P0.5mm_EP1.8x1.8mm; MPN CH343P; LCSC C2846043
U6: ATECC608C-SSHDA-T; SOIC-8_3.9x4.9mm_P1.27mm; MPN ATECC608C-SSHDA-T; LCSC C28975195
U7: W25Q128JVSIQ; SOIC-8_5.3x5.3mm_P1.27mm; MPN W25Q128JVSIQ; LCSC C97521
Y1: 12MHz; RPi_Crystal_SMD_3225-4Pin_3.2x2.5mm; MPN X322512MSB4SI; LCSC C9002

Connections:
+1V1: C4.1, C16.1, C17.1, C18.1, TP10.1, U1.6 (DVDD), U1.23 (DVDD), U1.39 (DVDD), U4.5 (OUT)
+3V3: C2.1, C3.1, C7.1, C10.1, C11.1, C12.1, C13.1, C14.1, C15.1, C19.1, C20.1, C23.1, C24.1, C25.1, C26.1, J2.7 (VDD), R7.2, R8.2, R13.2, TP5.1, U1.1 (IOVDD), U1.11 (IOVDD), U1.20 (IOVDD), U1.30 (IOVDD), U1.38 (IOVDD), U1.44 (ADC_AVDD), U1.45 (IOVDD), U1.46 (VREG_AVDD), U1.49 (VREG_VIN), U1.53 (USB_OTP_VDD), U1.54 (QSPI_IOVDD), U3.2 (VOUT), U4.1 (IN), U4.3 (EN), U5.1 (VIO), U6.8 (VCC), U7.8 (VCC)
/BL_GATE: Q1.1 (G), Q2.3 (D), R9.1
/BL_SW: Q1.3 (D), R11.1
/BTN_D0: SW1.2, U1.4 (GPIO2)
/BTN_D1: SW2.2, U1.5 (GPIO3)
/BTN_D2: SW3.1, U1.9 (GPIO6)
/CC1: J1.A5 (CC1), R1.1
/CC2: J1.B5 (CC2), R2.1
/CH_V3: C6.1, U5.6 (V3)
/LCD_BL: Q2.1 (G), R10.1, U1.17 (GPIO13)
/LCD_CS: J2.8 (CS), U1.13 (GPIO9)
/LCD_DC: J2.4 (RS), U1.12 (GPIO8)
/LCD_LEDA: J2.1 (LEDA), R11.2
/LCD_MOSI: J2.5 (SDA), U1.15 (GPIO11)
/LCD_RST: J2.3 (RESET), U1.16 (GPIO12)
/LCD_SCK: J2.6 (SCL), U1.14 (GPIO10)
/LED: D1.2 (A), U1.37 (GPIO25)
/LED_K: D1.1 (K), R12.1
/LINK_RX: TP13.1, U1.33 (GPIO21), U5.4 (TXD)
/LINK_TX: R13.1, TP12.1, U1.32 (GPIO20), U5.5 (RXD)
/QSPI_SCLK: U1.56 (QSPI_SCLK), U7.6 (CLK)
/QSPI_SD0: U1.57 (QSPI_SD0), U7.5 (DI/IO0)
/QSPI_SD1: U1.59 (QSPI_SD1), U7.2 (DO/IO1)
/QSPI_SD2: U1.58 (QSPI_SD2), U7.3 (~WP/IO2)
/QSPI_SD3: U1.55 (QSPI_SD3), U7.7 (~HOLD/IO3)
/QSPI_SS: U1.60 (~QSPI_SS), U7.1 (~CS)
/RUN: TP4.1, U1.26 (RUN)
/SCL: R8.1, U1.8 (GPIO5), U6.6 (SCL)
/SDA: R7.1, U1.7 (GPIO4), U6.5 (SDA)
/SWCLK: R14.1, U1.24 (SWCLK)
/SWCLK_J: J3.1 (SWCLK), R14.2, TP1.1
/SWDIO: R15.1, U1.25 (SWDIO)
/SWDIO_J: J3.3 (SWDIO), R15.2, TP3.1
/USB_D+: J1.A6 (D+), J1.B6 (D+), U2.1 (I/O1), U2.6 (I/O1), U5.7 (UD+)
/USB_D-: J1.A7 (D-), J1.B7 (D-), U2.3 (I/O2), U2.4 (I/O2), U5.8 (UD-)
/XIN: C21.1, U1.21 (XIN), Y1.1
/XOUT: R3.1, U1.22 (XOUT)
/XTAL_OUT: C22.1, R3.2, Y1.3
GND: C1.2, C2.2, C3.2, C4.2, C5.2, C6.2, C7.2, C10.2, C11.2, C12.2, C13.2, C14.2, C15.2, C16.2, C17.2, C18.2, C19.2, C20.2, C21.2, C22.2, C23.2, C24.2, C25.2, C26.2, J1.A1 (GND), J1.A12 (GND), J1.B1 (GND), J1.B12 (GND), J1.SH (SHIELD), J2.2 (GND), J3.2 (GND), J3.SH (TABS), Q2.2 (S), R1.2, R2.2, R10.2, R12.2, SW1.1, SW2.1, SW3.2, TP2.1, TP9.1, U1.47 (VREG_PGND), U1.50 (VREG_FB), U1.61 (GND), U2.2 (GND), U3.1 (GND), U4.2 (GND), U5.2 (GND), U5.17 (EP), U6.4 (GND), U7.4 (GND), Y1.2, Y1.4
VBUS: C1.1, C5.1, J1.A4 (VBUS), J1.A9 (VBUS), J1.B4 (VBUS), J1.B9 (VBUS), Q1.2 (S), R9.2, TP11.1, U2.5 (VBUS), U3.3 (VIN), U5.3 (VDD5), U5.9 (VBUS)

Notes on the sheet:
Power in. 5.1k on each CC. 5.7u on VBUS. U3: 5 V to 3.3 V. U4: 3.3 V to the core's 1.1 V.
The link: USB to UART1 and nothing else. DTR and RTS reach nothing.
The RP2350A. Its own core regulator is not used: FB to ground, LX open, its supplies on 3.3 V (datasheet, figure 24).
The key that signs: I2C0, 4.7k pull-ups.
The screen's ribbon, and its backlight from 5 V: GPIO13 high is on.
The flash, 16 MB. Left off when U1 is an RP2354A, which has its own inside (BUILD).
D0, D1, D2 to ground; the LED.
The way in for firmware: SWD on J3 and the pads on the back. Nothing here is reached through the USB-C.

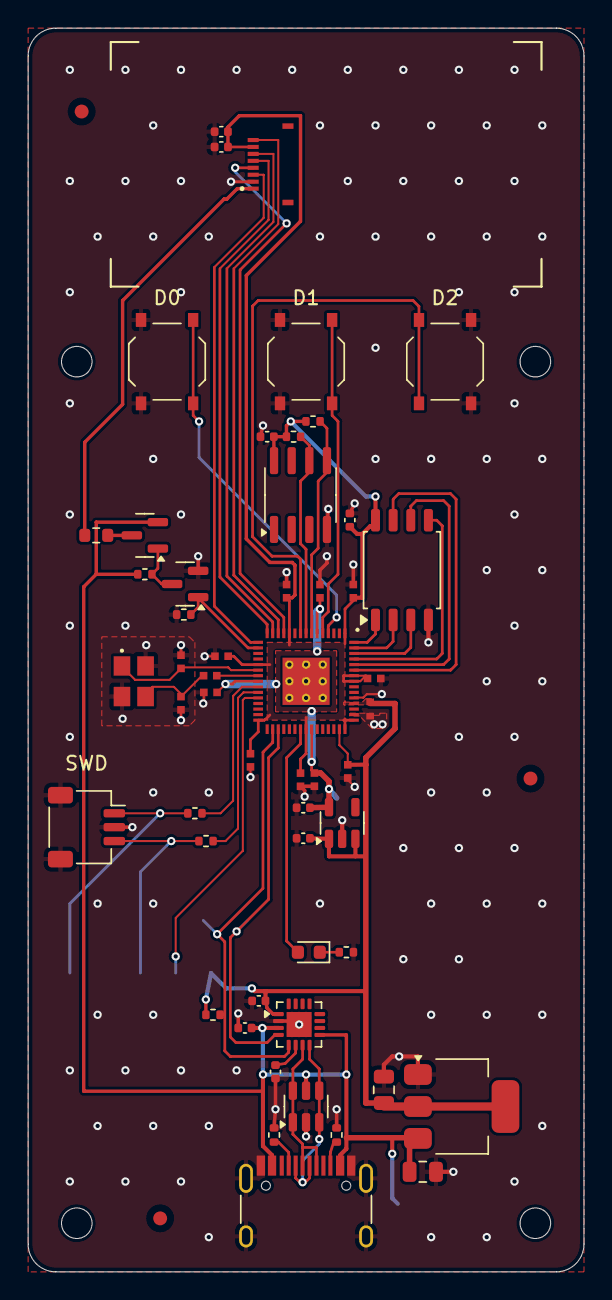
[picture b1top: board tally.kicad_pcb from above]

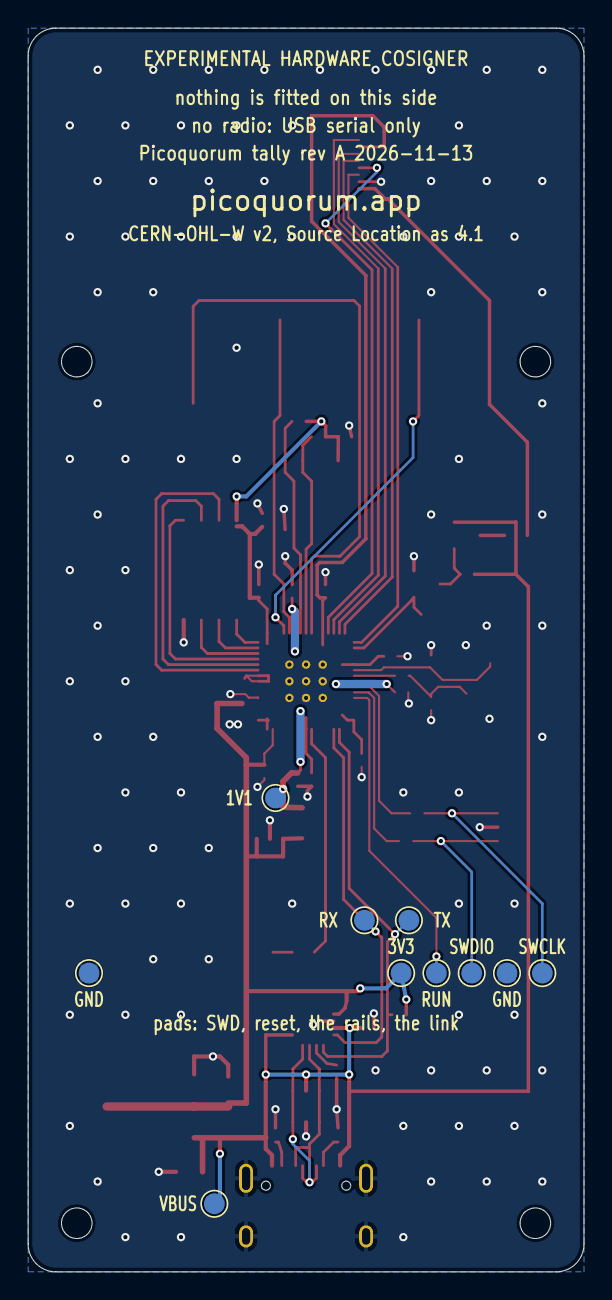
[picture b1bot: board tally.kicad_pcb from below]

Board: 2 copper layers, 40.0 x 89.5 mm, 70 parts (10 on the bottom side), 41 nets.

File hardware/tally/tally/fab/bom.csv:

Comment,Designator,Footprint,LCSC Part #
4.7u,"C1,C4",C_0402_1005Metric,C23733
10u,C2,C_0805_2012Metric,C15850
1u,"C3,C5,C25",C_0402_1005Metric,C52923
100n,"C6,C7,C23,C24,C26",C_0402_1005Metric,C1525
100n,"C10,C11,C12,C13,C14,C15,C16,C17,C19",RPi_C_0402,C1525
4.7u,C18,RPi_C_0402,C23733
4.7u,C20,RPi_C_0402_wide,C23733
15p,"C21,C22",RPi_C_0402,C1548
RED,D1,LED_0603_1608Metric,C2286
USB-C,J1,USB_C_Receptacle_HRO_TYPE-C-31-M-12,C165948
PANEL,J2,FPC_ZIF_8P_P0.5mm_HDGC_0.5K-HX-8PWB,C2919492
SWD,J3,JST_SH_SM03B-SRSS-TB_1x03-1MP_P1.00mm_Horizontal,C160403
AO3401A,Q1,SOT-23,C15127
AO3400A,Q2,SOT-23,C20917
5.1k,"R1,R2",R_0402_1005Metric,C25905
1k,R3,RPi_R_0402,C11702
4.7k,"R7,R8,R9,R10",R_0402_1005Metric,C25900
150R,R11,R_0603_1608Metric,C22808
1k,R12,R_0402_1005Metric,C11702
D0,SW1,SW_Push_1P1T_XKB_TS-1187A,C318884
D1,SW2,SW_Push_1P1T_XKB_TS-1187A,C318884
D2,SW3,SW_Push_1P1T_XKB_TS-1187A,C318884
RP2350A,U1,RPi_RP2350A_QFN-60_7x7mm_P0.4mm_ThermalVias,C42411118
USBLC6-2SC6,U2,SOT-23-6,C7519
LDL1117S33R,U3,SOT-223-3_TabPin2,C435835
TLV74311PDBVR,U4,SOT-23-5,C485147
CH343P,U5,WCH_QFN-16-1EP_3x3mm_P0.5mm_EP1.8x1.8mm,C2846043
ATECC608C-SSHDA-T,U6,SOIC-8_3.9x4.9mm_P1.27mm,C28975195
W25Q128JVSIQ,U7,SOIC-8_5.3x5.3mm_P1.27mm,C97521
12MHz,Y1,RPi_Crystal_SMD_3225-4Pin_3.2x2.5mm,C9002

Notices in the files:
hardware/README.md:
Copyright Jason McPheron 2026.
This source describes Open Hardware and is licensed under the CERN-OHL-W v2
([LICENSE-HARDWARE](../LICENSE-HARDWARE), https://ohwr.org/cern_ohl_w_v2.txt). You may redistribute
and modify this source and make products using it under the terms of the CERN-OHL-W v2. This source
is distributed WITHOUT ANY EXPRESS OR IMPLIED WARRANTY, INCLUDING OF MERCHANTABILITY, SATISFACTORY
QUALITY AND FITNESS FOR A PARTICULAR PURPOSE. Please see the CERN-OHL-W v2 for applicable
conditions.
Source Location:** https://github.com/jmcpheron/pico-quorum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
